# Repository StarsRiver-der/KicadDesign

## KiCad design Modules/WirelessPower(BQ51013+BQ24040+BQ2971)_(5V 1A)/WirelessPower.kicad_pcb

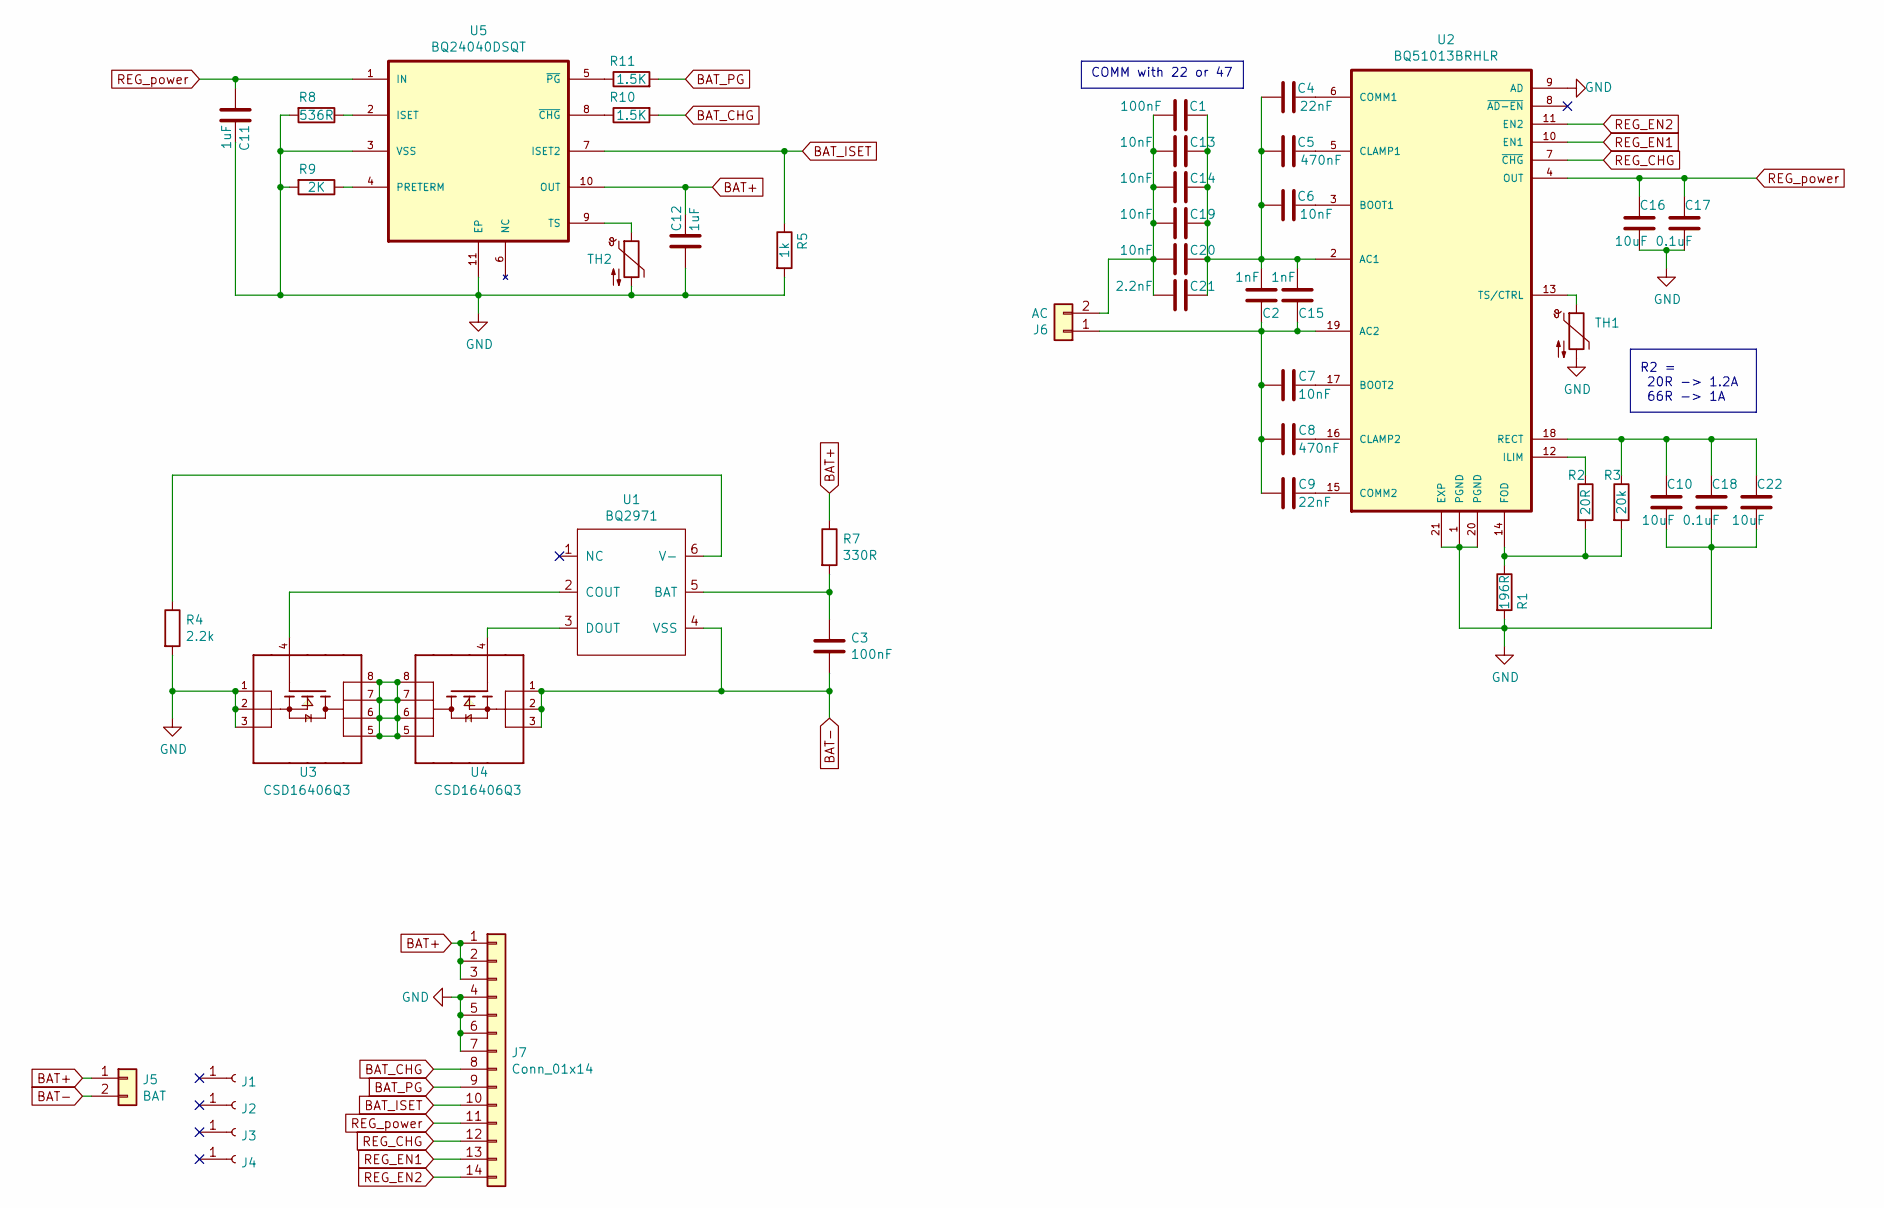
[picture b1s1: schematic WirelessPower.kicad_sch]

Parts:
C1: 100nF; C_1206_3216Metric
C2, C15: 1nF; C_0603_1608Metric
C3: 100nF; C_0402_1005Metric
C4, C9: 22nF; C_0402_1005Metric
C5, C8: 470nF; C_0402_1005Metric
C6, C7: 10nF; C_0402_1005Metric
C10, C16, C22: 10uF; C_0603_1608Metric
C11, C12: 1uF; C_0603_1608Metric
C13, C14, C19, C20: 10nF; C_0603_1608Metric
C17, C18: 0.1uF; C_0603_1608Metric
C21: 2.2nF; C_0603_1608Metric
J1, J2, J3, J4: Conn_01x01_Female; MountingHole_2.2mm_M2
J5: BAT; PinHeader_1x02_P2.54mm_Vertical
J6: AC; R_Axial_DIN0204_L3.6mm_D1.6mm_P2.54mm_Vertical
J7: Conn_01x14; Hirose_FH12-14S-0.5SH_1x14-1MP_P0.50mm_Horizontal
R1: 196R; R_0402_1005Metric
R2: 20R; R_0402_1005Metric
R3: 20k; R_0402_1005Metric
R4: 2.2k; R_0402_1005Metric
R5: 1k; R_0402_1005Metric
R7: 330R; R_0402_1005Metric
R8: 536R; R_0402_1005Metric
R9: 2K; R_0402_1005Metric
R10, R11: 1.5K; R_0402_1005Metric
TH1, TH2: Thermistor_NTC; R_Axial_DIN0204_L3.6mm_D1.6mm_P2.54mm_Vertical
U1: BQ2971; WSON-6_1.5x1.5mm_P0.5mm
U2: BQ51013BRHLR; IC_MSP430FR2522IRHLR
U3, U4: CSD16406Q3
U5: BQ24040DSQT; SON40P200X200X80-11N

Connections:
BAT+: C12.1, J5.1, J7.1, J7.2, J7.3, R7.1, U5.10 (OUT); also elsewhere on the board
BAT-: C3.2, J5.2, U1.4 (VSS), U4.1, U4.2, U4.3; also elsewhere on the board
BAT_CHG: J7.8, R10.2
BAT_ISET: J7.10, R5.1, U5.7 (ISET2)
BAT_PG: J7.9, R11.2
GND: C10.1, C11.1, C12.2, C16.1, C17.1, C18.1, C22.1, J7.4, J7.5, J7.6, J7.7, R1.2, R4.2, R5.2, R8.2, R9.2, TH1.2, TH2.2, U2.1 (PGND), U2.9 (AD), U2.20 (PGND), U2.21 (EXP), U3.1, U3.2, U3.3, U5.3 (VSS), U5.11 (EP)
unnamed: C1.1, C13.1, C14.1, C19.1, C20.1, C21.1, J6.2
unnamed: C1.2, C2.1, C4.1, C5.1, C6.1, C13.2, C14.2, C15.1, C19.2, C20.2, C21.2, U2.2 (AC1)
unnamed: C3.1, R7.2, U1.5 (BAT)
unnamed: C4.2, U2.6 (COMM1)
unnamed: C5.2, U2.5 (CLAMP1)
unnamed: C6.2, U2.3 (BOOT1)
unnamed: C7.1, U2.17 (BOOT2)
unnamed: C8.1, U2.16 (CLAMP2)
unnamed: C9.1, U2.15 (COMM2)
unnamed: C10.2, C18.2, C22.2, R3.1, U2.18 (RECT)
unnamed: C2.2, C7.2, C8.2, C9.2, C15.2, J6.1, U2.19 (AC2)
unnamed: R1.1, R2.2, R3.2, U2.14 (FOD)
unnamed: R2.1, U2.12 (ILIM)
unnamed: R4.1, U1.6 (V-)
unnamed: R8.1, U5.2 (ISET)
unnamed: R9.1, U5.4 (PRETERM)
unnamed: R10.1, U5.8 (~CHG)
unnamed: R11.1, U5.5 (~PG)
unnamed: TH1.1, U2.13 (TS/CTRL)
unnamed: TH2.1, U5.9 (TS)
unnamed: U1.2 (COUT), U3.4
unnamed: U1.3 (DOUT), U4.4
unnamed: U3.5, U3.6, U3.7, U3.8, U4.5, U4.6, U4.7, U4.8
REG_CHG: J7.12, U2.7 (~CHG)
REG_EN1: J7.13, U2.10 (EN1)
REG_EN2: J7.14, U2.11 (EN2)
REG_power: C11.2, C16.2, C17.2, J7.11, U2.4 (OUT), U5.1 (IN)

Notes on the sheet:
R2 = 20R -> 1.2A 66R -> 1A
COMM with 22 or 47

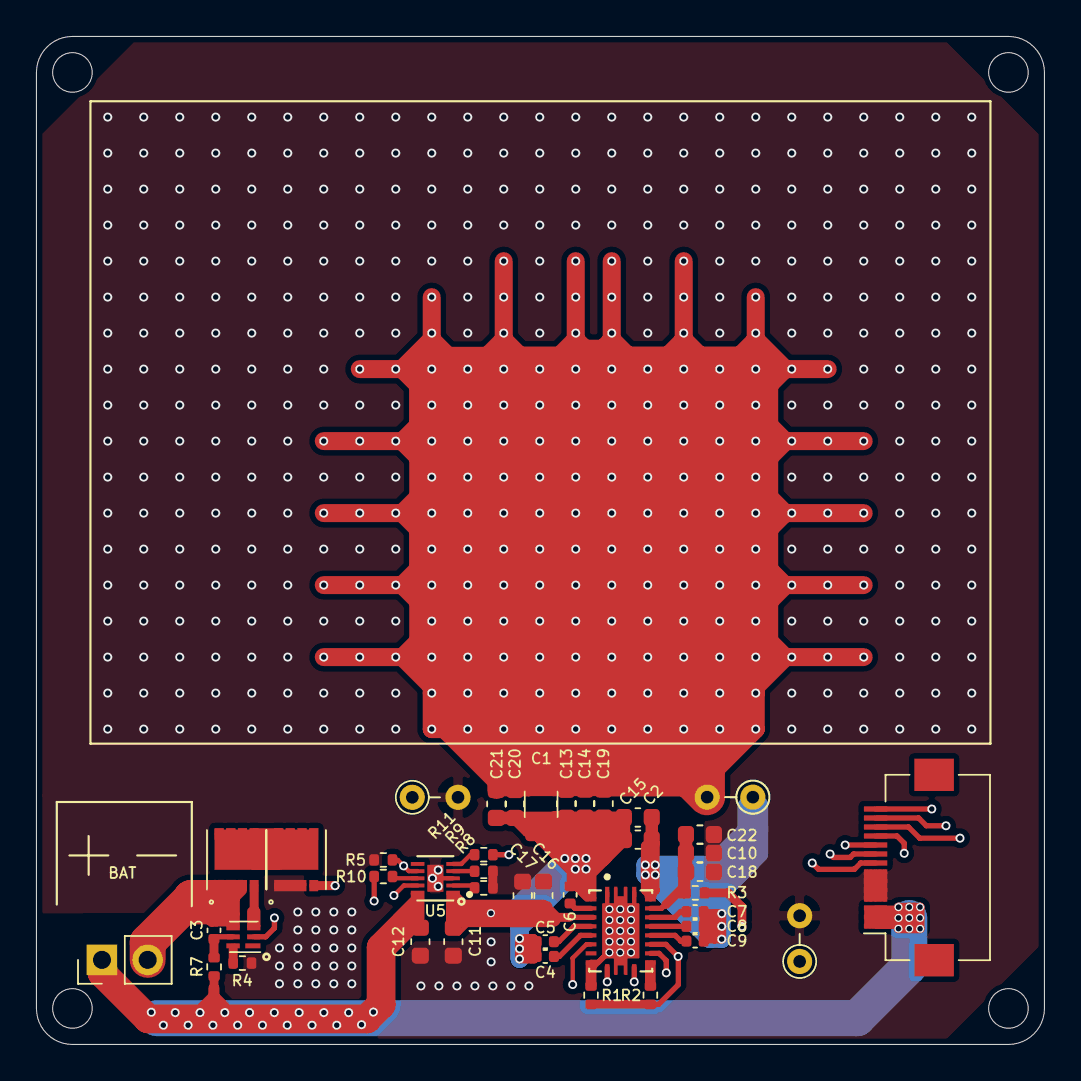
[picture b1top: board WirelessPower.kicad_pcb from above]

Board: 4 copper layers, 56.0 x 56.0 mm, 46 parts (0 on the bottom side), 33 nets.

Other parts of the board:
BAT: BAT; PinHeader_1x02_P2.54mm_Vertical

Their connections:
BAT+: BAT.1; also elsewhere on the board
BAT-: BAT.2; also elsewhere on the board

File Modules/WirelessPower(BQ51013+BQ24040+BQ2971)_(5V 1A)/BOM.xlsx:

代号 | 值 | 类型 | 封装 | 数量 | 单价
C1 | 100nF | C 耐压 50V | 0402 | 100
C2, C15 | 1nF | C 耐压 50V | 0402 | 100
C3 | 0.1uF | C 耐压 50V | 0402 | 100
C4, C9, C14 | 22nF | C 耐压 50V | 0402 | 100
C5, C8 | 470nF | C 耐压 50V | 0402 | 100
C6, C7 | 10nF | C 耐压 50V | 0402 | 100
C10, C16 | 10uF | C 耐压 100V | 0603 | 100
C11, C12 | 1uF | C 耐压 50V | 0402 | 100
C13 | 20nF | C 耐压 50V | 0402 | 100
C17, C18 | 0.1uF | C 耐压 100V | 0603 | 100
R1 | 196R | R | 0402 | 100
R2 | 66R | R | 0402 | 100
R3 | 20k | R | 0402 | 100
R4 | 2.2k | R | 0402 | 100
R5 | 1k | R | 0402 | 100
R7 | 330R | R | 0402 | 100
R8 | 640R | R | 0402 | 100
R9 | 2K | R | 0402 | 100
R10, R11 | 1.5K | R | 0402 | 100
D1 | 红 | LED | 0402 | 50
U2 | BQ51013BRHLR | BQ51013BRHLR | BQ51013BRHLR | 1
U5 | BQ24040DSQT | BQ24040DSQT | BQ24040DSQT | 1
备注：元件用于ESD电路，电容耐压一定要高，防止击穿

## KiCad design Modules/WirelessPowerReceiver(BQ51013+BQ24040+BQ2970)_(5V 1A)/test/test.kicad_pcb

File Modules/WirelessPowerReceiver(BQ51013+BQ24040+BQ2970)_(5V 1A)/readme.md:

# 无线充电接收器
* 工作温度：0-55℃
* 电池直接输出模式
* 电池端最高受电功率 4.1V x 0.98A
* 最高接收功率 5V x 1.12A

# 原理
见说明手册

# 接口
* 电池：2.5mm_2P
* 输出和无线充电电流控制：FPC_Hirose_FH12-14S

# 预览
_(5V%201A)/preview.jpg)

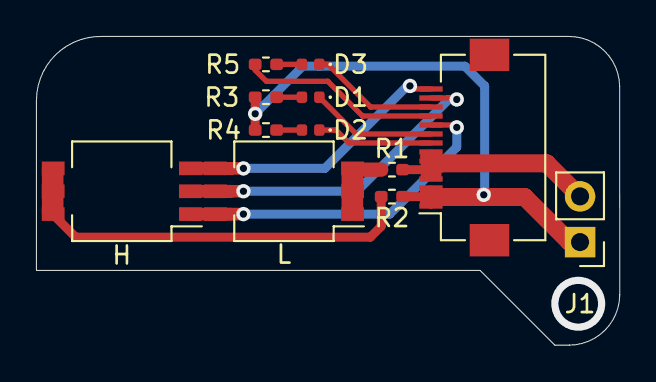
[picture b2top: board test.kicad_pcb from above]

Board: 2 copper layers, 32.4 x 17.1 mm, 12 parts (0 on the bottom side), 14 nets.

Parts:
D1, D2, D3: LED; LED_0402_1005Metric
H: SW_DIP_x03; SW_DIP_SPSTx03_Slide_KingTek_DSHP03TS_W7.62mm_P1.27mm
J1: Conn_01x02; PinHeader_1x02_P2.54mm_Vertical
J7: Conn_01x14; Hirose_FH12-14S-0.5SH_1x14-1MP_P0.50mm_Horizontal
L: SW_DIP_x03; SW_DIP_SPSTx03_Slide_KingTek_DSHP03TS_W7.62mm_P1.27mm
R1, R2: 1K; R_0402_1005Metric_Pad0.72x0.64mm_HandSolder
R3, R4, R5: R; R_0402_1005Metric_Pad0.72x0.64mm_HandSolder

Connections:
BAT+: J1.1, J7.1, J7.2, J7.3, R2.1, R3.2, R4.2
BAT_CHG: D2.1 (K), J7.8
BAT_ISET: H.1, J7.10, L.6
BAT_PG: D1.1 (K), J7.9
GND: J1.2, J7.4, J7.5, J7.6, J7.7, R1.2
unnamed: D1.2 (A), R3.1
unnamed: D2.2 (A), R4.1
unnamed: D3.2 (A), R5.1
unnamed: L.1, L.2, L.3, R1.1
unnamed: H.4, H.5, H.6, R2.2
REG_CHG: D3.1 (K), J7.12
REG_EN1: H.2, J7.13, L.5
REG_EN2: H.3, J7.14, L.4
REG_power: J7.11, R5.2

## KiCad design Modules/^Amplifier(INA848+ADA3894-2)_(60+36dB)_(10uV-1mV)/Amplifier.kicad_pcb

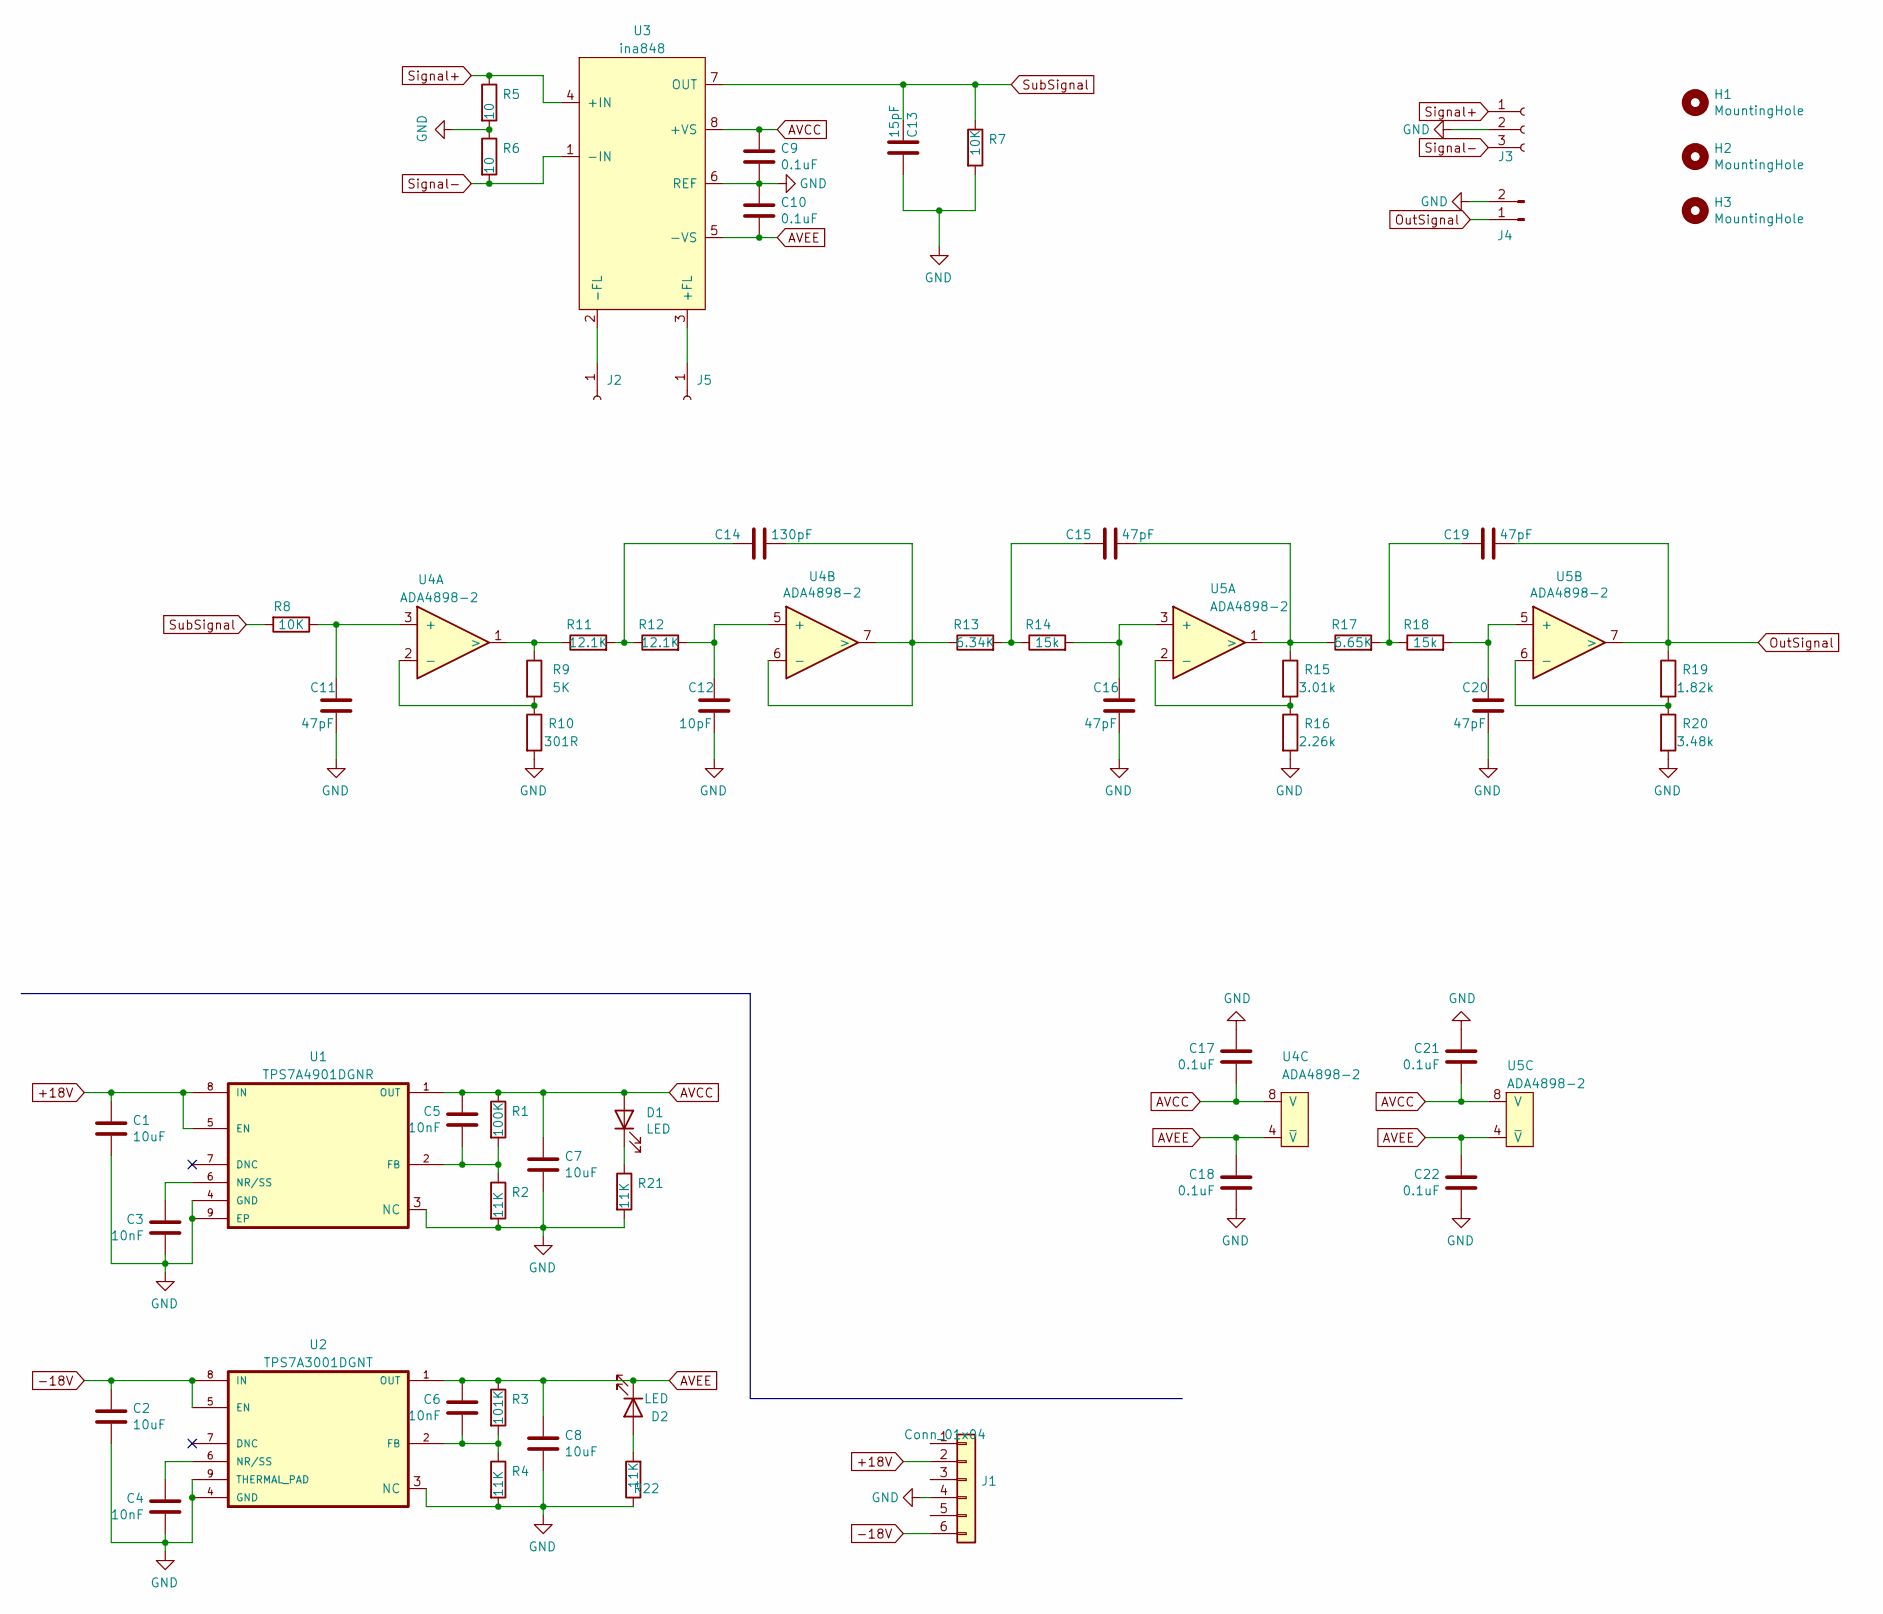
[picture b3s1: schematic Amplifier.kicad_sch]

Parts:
C1, C2, C7, C8: 10uF; C_0603_1608Metric
C3, C4, C5, C6: 10nF; C_0402_1005Metric
C9, C10, C17, C18, C21, C22: 0.1uF; C_1206_3216Metric
C11, C15, C16, C19, C20: 47pF; C_0402_1005Metric
C12: 10pF; C_0402_1005Metric
C13: 15pF; C_0402_1005Metric
C14: 130pF; C_0402_1005Metric
D1, D2: LED; LED_0402_1005Metric
H1, H2, H3: MountingHole; MountingHole_2.2mm_M2
J1: Conn_01x04; Multicomp_MC9A12-1034_2x03_P2.54mm_Vertical
J2, J5: Conn_01x01_Female; MountingPad_1mm
J3: Conn_01x03_Female; PinSocket_1x03_P2.54mm_Vertical
J4: Conn_01x02_Male; SMA_Amphenol_132134_Vertical
R1: 100K; R_0402_1005Metric
R2, R4, R21, R22: 11K; R_0402_1005Metric
R3: 101K; R_0402_1005Metric
R5, R6: 10; R_0402_1005Metric
R7, R8: 10K; R_0402_1005Metric
R9: 5K; R_0402_1005Metric
R10: 301R; R_0402_1005Metric
R11, R12: 12.1K; R_0402_1005Metric
R13: 6.34K; R_0402_1005Metric
R14, R18: 15k; R_0402_1005Metric
R15: 3.01k; R_0402_1005Metric
R16: 2.26k; R_0402_1005Metric
R17: 6.65K; R_0402_1005Metric
R19: 1.82k; R_0402_1005Metric
R20: 3.48k; R_0402_1005Metric
U1: TPS7A4901DGNR; SOP65P490X110-9N
U2: TPS7A3001DGNT; SOP65P490X110-9N
U3: ina848; SOIC-8_3.9x4.9mm_P1.27mm
U4, U5: ADA4898-2; SOIC-8-1EP_3.9x4.9mm_P1.27mm_EP2.29x3mm

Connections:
+18V: C1.1, J1.2, U1.5 (EN), U1.8 (IN)
-18V: C2.1, J1.6, U2.5 (EN), U2.8 (IN)
AVCC: C5.1, C7.1, C9.1, C17.2, C21.2, D1.2 (A), R1.1, U1.1 (OUT), U3.8 (+VS), U4.8 (V), U5.8 (V)
AVEE: C6.1, C8.1, C10.2, C18.1, C22.1, D2.1 (K), R3.1, U2.1 (OUT), U3.5 (-VS), U4.4 (~V), U5.4 (~V)
GND: C1.2, C2.2, C3.2, C4.2, C7.2, C8.2, C9.2, C10.1, C11.2, C12.2, C13.2, C16.2, C17.1, C18.2, C20.2, C21.1, C22.2, J1.4, J3.2, J4.2, R2.2, R4.2, R5.2, R6.1, R7.2, R10.2, R16.2, R20.2, R21.2, R22.1, U1.3 (NC), U1.4 (GND), U1.9 (EP), U2.3 (NC), U2.4 (GND), U2.9 (THERMAL_PAD), U3.6 (REF)
unnamed: C3.1, U1.6 (NR/SS)
unnamed: C4.1, U2.6 (NR/SS)
unnamed: C5.2, R1.2, R2.1, U1.2 (FB)
unnamed: C6.2, R3.2, R4.1, U2.2 (FB)
unnamed: C11.1, R8.1, U4.3 (+)
unnamed: C12.1, R12.2, U4.5 (+)
unnamed: C14.1, R11.2, R12.1
unnamed: C14.2, R13.1, U4.6 (-), U4.7 (>)
unnamed: C15.1, R13.2, R14.1
unnamed: C15.2, R15.1, R17.1, U5.1 (>)
unnamed: C16.1, R14.2, U5.3 (+)
unnamed: C19.1, R17.2, R18.1
unnamed: C20.1, R18.2, U5.5 (+)
unnamed: D1.1 (K), R21.1
unnamed: D2.2 (A), R22.2
unnamed: J2.1, U3.2 (-FL)
unnamed: J5.1, U3.3 (+FL)
unnamed: R9.2, R10.1, U4.2 (-)
unnamed: R9.1, R11.1, U4.1 (>)
unnamed: R15.2, R16.1, U5.2 (-)
unnamed: R19.2, R20.1, U5.6 (-)
OutSignal: C19.2, J4.1, R19.1, U5.7 (>)
Signal+: J3.1, R5.1, U3.4 (+IN)
Signal-: J3.3, R6.2, U3.1 (-IN)
SubSignal: C13.1, R7.1, R8.2, U3.7 (OUT)

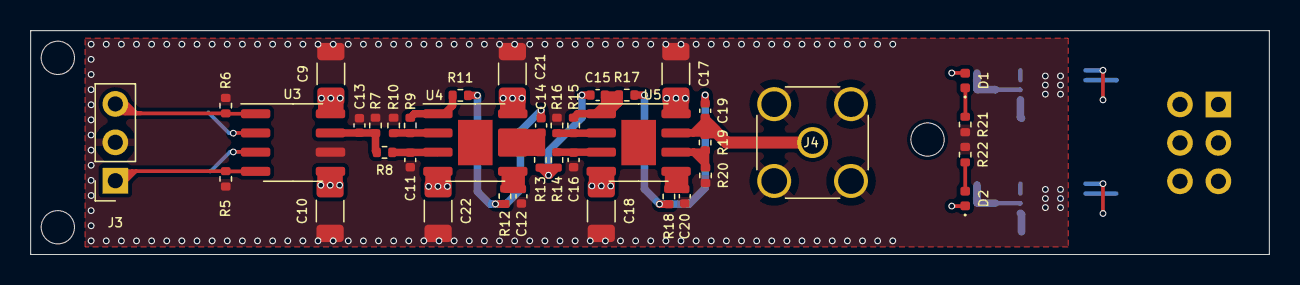
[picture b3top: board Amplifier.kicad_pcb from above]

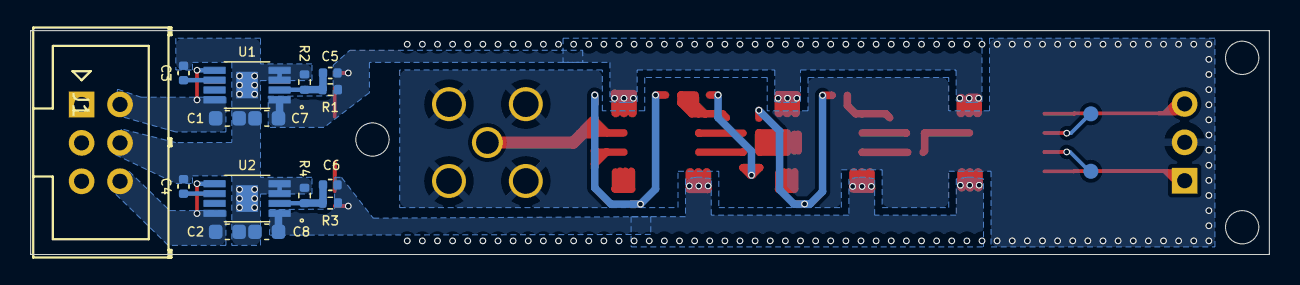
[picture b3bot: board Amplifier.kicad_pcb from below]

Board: 4 copper layers, 81.9 x 14.8 mm, 59 parts (17 on the bottom side), 30 nets.

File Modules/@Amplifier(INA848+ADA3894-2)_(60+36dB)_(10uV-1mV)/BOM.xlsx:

符号 | 数量/板 | 值 | 备注 | 封装 | 数量 | 单价 | 总价
C1, C2, C7, C8 | 4 | 10uF | 25V | 0603 | 100 | 0.1
C3, C4, C5, C6 | 4 | 10nF | 25V | 0402 | 100 | 1.4999999999999999E-2
C9, C10, C17, C18, C21, C22 | 6 | 100nF | 25V COG高频电容 | 1206 | 50
C11, C15, C16, C19, C20 | 5 | 47pF | 25V | 0402 | 100 | 1.4999999999999999E-2
C12 | 1 | 10pF | 25V | 0402 | 100 | 1.4999999999999999E-2
C13 | 1 | 15pF | 25V | 0402 | 100 | 1.4999999999999999E-2
C14 | 1 | 130pF | 25V | 0402 | 100 | 1.4999999999999999E-2
D1, D2 | 2 | LED |  | 0402 | 100
R1 | 1 | 100K |  | 0402 | 100 | 0.01
R2, R4, R21, R22 | 4 | 11K |  | 0402 | 100 | 0.01
R3 | 1 | 101K |  | 0402 | 100 | 0.01
R5, R6 | 2 | 10R |  | 0402 | 100 | 0.01
R7, R8 | 2 | 10K |  | 0402 | 100 | 0.01
R9 | 1 | 5K |  | 0402 | 100 | 0.01
R10 | 1 | 301R |  | 0402 | 100 | 0.01
R11, R12 | 2 | 12.1K |  | 0402 | 100 | 0.01
R13 | 1 | 6.34K |  | 0402 | 100 | 0.01
R14, R18 | 2 | 15k |  | 0402 | 100 | 0.01
R15 | 1 | 3.01k |  | 0402 | 100 | 0.01
R16 | 1 | 2.26k |  | 0402 | 100 | 0.01
R17 | 1 | 6.65K |  | 0402 | 100 | 0.01
R19 | 1 | 1.82k |  | 0402 | 100 | 0.01
R20 | 1 | 3.48k |  | 0402 |  | 0.01
U1 | 1 | TPS7A4901DGNR | TPS7A4901DGNR:TPS7A4901DGNR |  | 5 | 8
U2 | 1 | TPS7A3001DGNT | TPS7A3001DGNT:TPS7A3001DGNT |  | 5 | 8
UX | 1 | ina849 | INA:ina849 | SOIC-8_3.9x4.9mm | 2
U3 | 1 | ina848 | INA:ina848 | SOIC-8_3.9x4.9mm | 2
U4, U5 | 2 | ADA4898-2 | ADA:ADA4898-2 | SOIC-8_3.9x4.9mm | 2

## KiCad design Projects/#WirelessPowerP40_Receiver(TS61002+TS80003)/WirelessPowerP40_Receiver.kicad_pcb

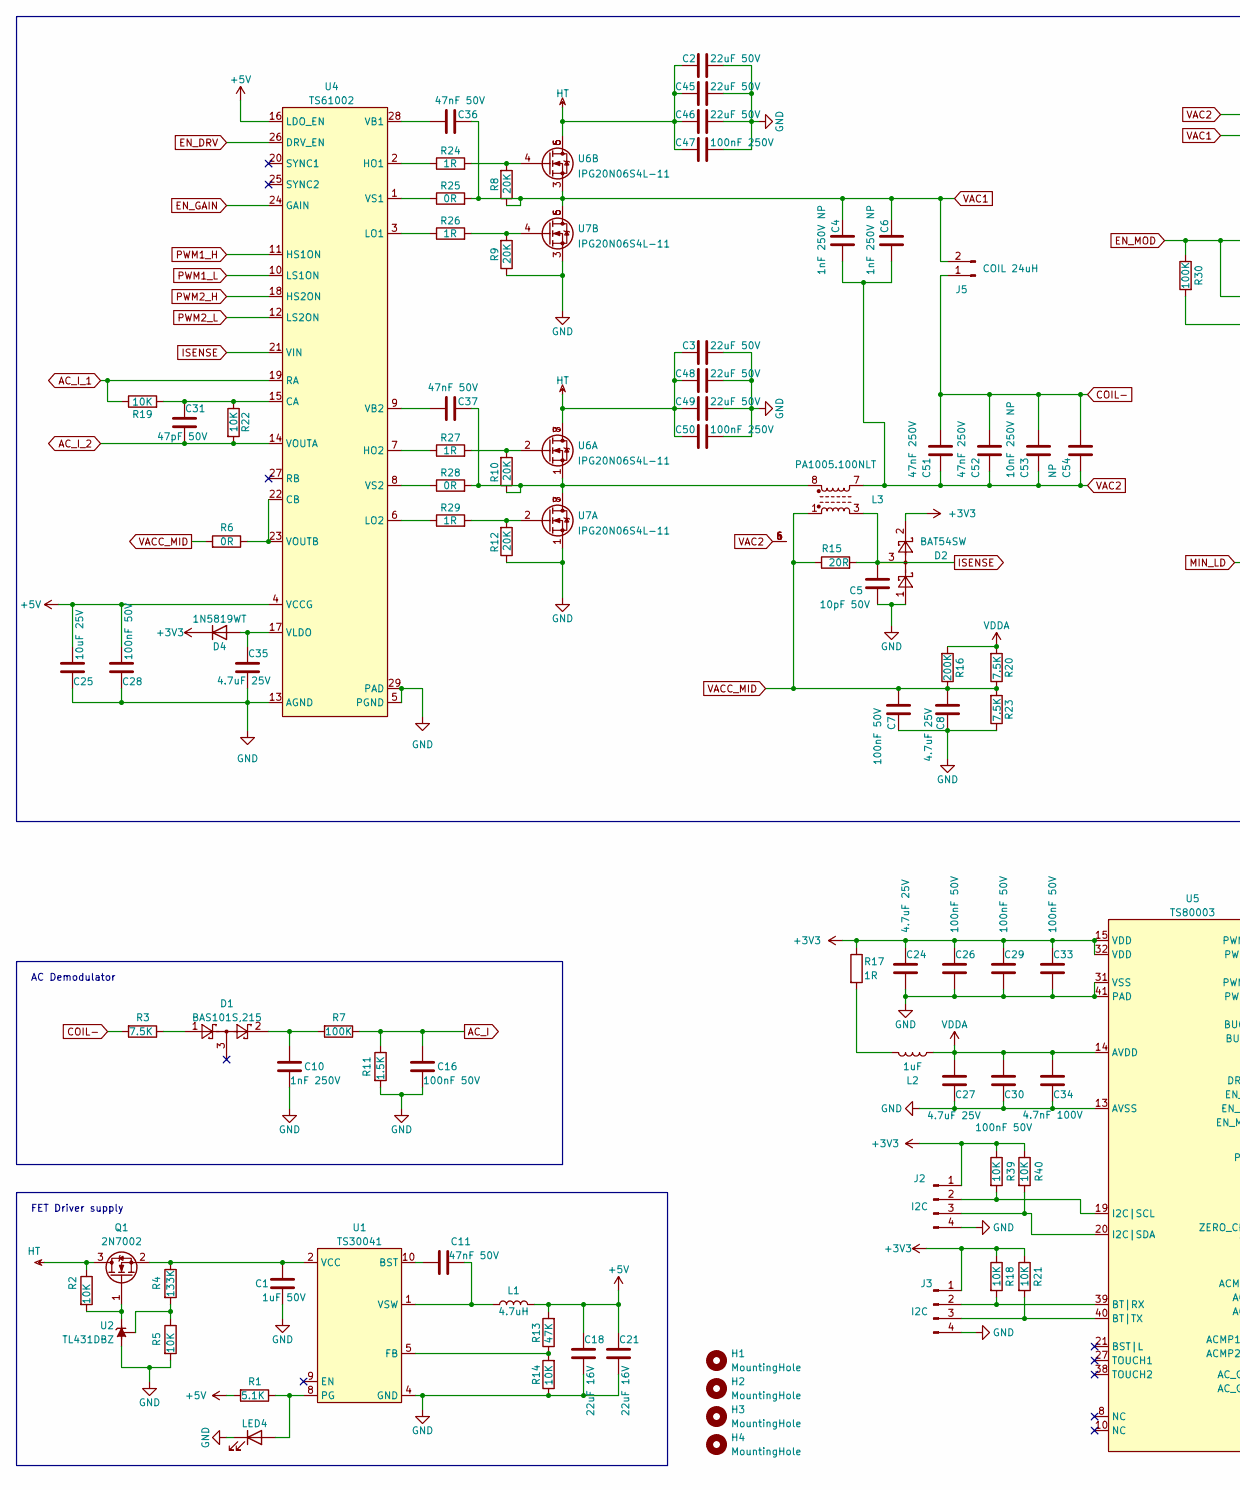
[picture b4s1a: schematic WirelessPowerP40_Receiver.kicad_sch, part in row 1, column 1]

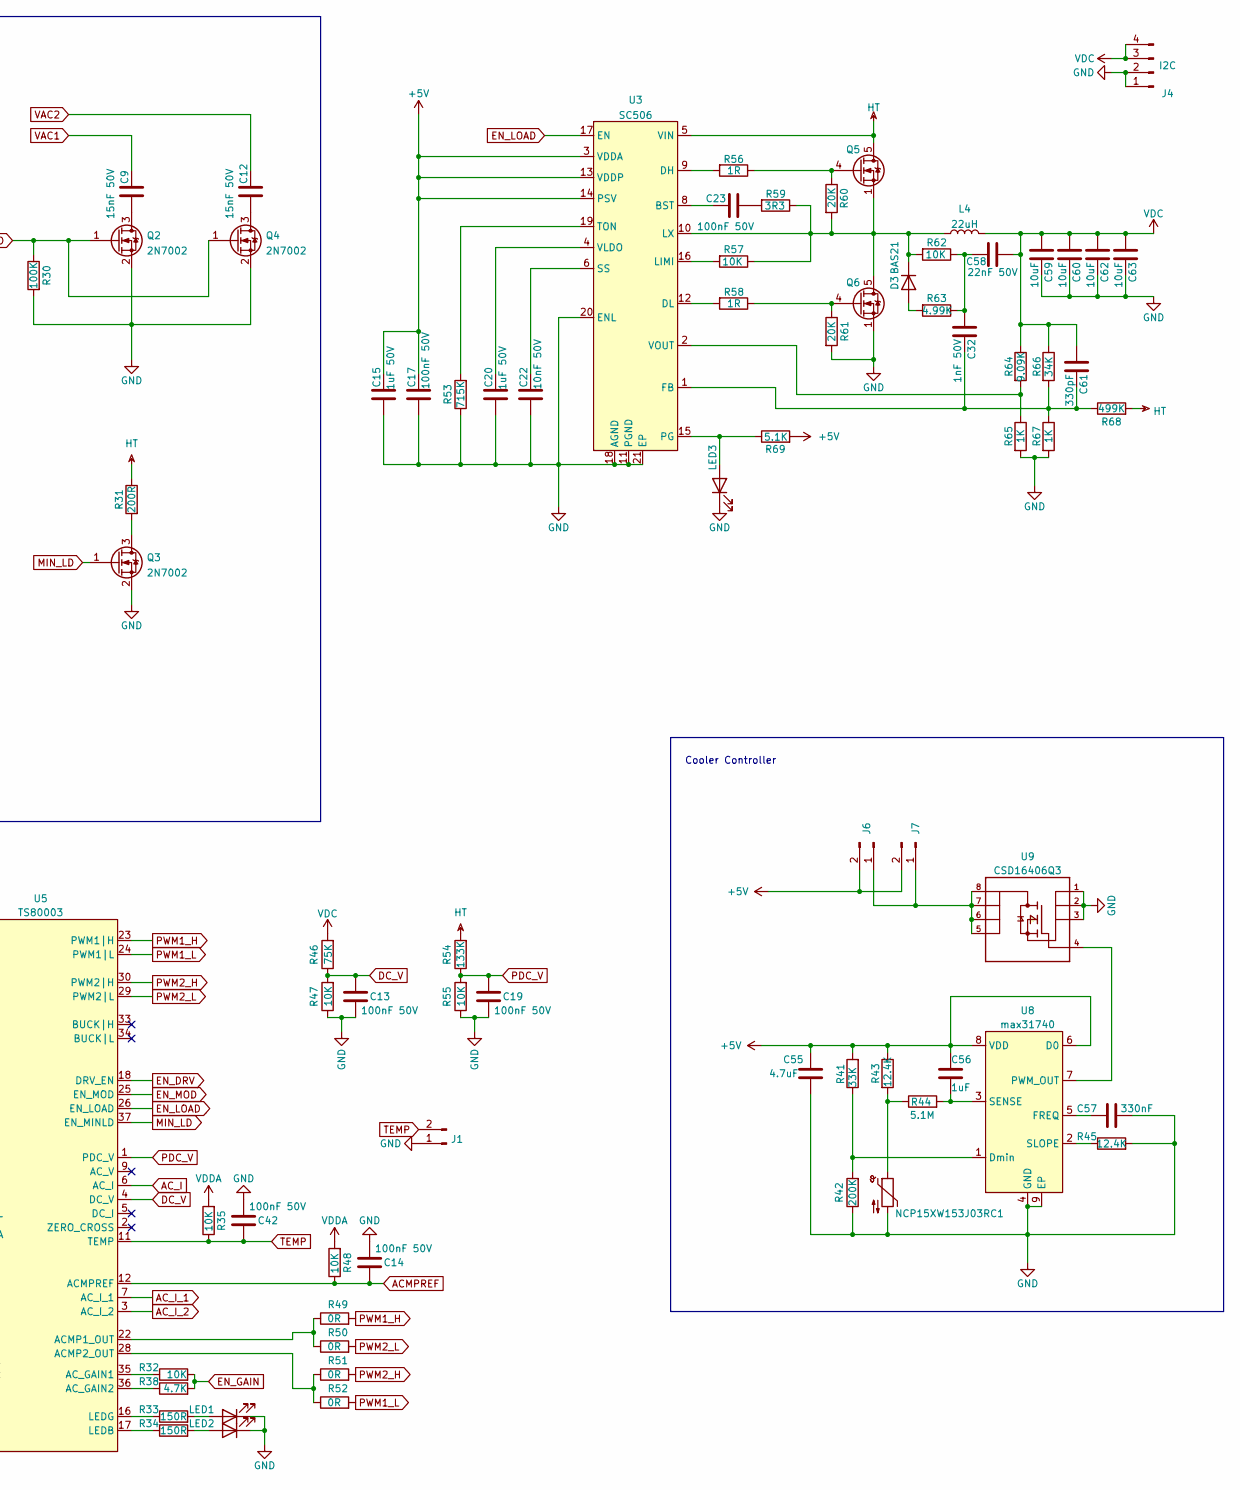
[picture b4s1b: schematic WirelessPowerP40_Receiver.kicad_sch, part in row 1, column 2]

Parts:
C1, C15, C20: 1uF 50V; C_0402_1005Metric
C2, C3, C45, C46, C48, C49: 22uF 50V; C_0805_2012Metric
C4, C6: 1nF 250V NP; C_0603_1608Metric
C5: 10pF 50V; C_0402_1005Metric
C7, C13, C14, C16, C17, C19, C23, C26, C28, C29, C30, C33, C42: 100nF 50V; C_0402_1005Metric
C8, C24, C27, C35: 4.7uF 25V; C_0402_1005Metric
C9, C12: 15nF 50V; C_0402_1005Metric
C10: 1nF 250V; C_0603_1608Metric
C11, C36, C37: 47nF 50V; C_0402_1005Metric
C18, C21: 22uF 16V; C_0603_1608Metric
C22: 10nF 50V; C_0402_1005Metric
C25: 10uF 25V; C_0603_1608Metric
C31: 47pF 50V; C_0402_1005Metric
C32: 1nF 50V; C_0402_1005Metric
C34: 4.7nF 100V; C_0402_1005Metric
C47, C50: 100nF 250V; C_0805_2012Metric
C51, C52: 47nF 250V; C_1210_3225Metric
C53: 10nF 250V NP; C_1210_3225Metric
C54: NP; C_1210_3225Metric
C55: 4.7uF; C_0402_1005Metric
C56: 1uF; C_0402_1005Metric
C57: 330nF; C_0402_1005Metric
C58: 22nF 50V; C_0402_1005Metric
C59, C60, C62, C63: 10uF; C_1206_3216Metric
C61: 330pF; C_0402_1005Metric
D1: BAS101S,215; SOT-23
D2: BAT54SW; SOT-323_SC-70
D3: BAS21; SOT-23
D4: 1N5819WT; D_SOD-523
H1, H2, H3, H4: MountingHole; MountingHole_2.2mm_M2_Pad_Via
J1, J6, J7: Conn_01x02_Male; PinHeader_1x02_P2.00mm_Vertical
J2, J3: I2C; PinHeader_1x04_P2.00mm_Vertical
J4: I2C; SolderWire-0.75sqmm_1x04_P4.8mm_D1.25mm_OD2.3mm
J5: COIL 24uH; AMASS_XT30U-F_1x02_P5.0mm_Vertical
L1: 4.7uH; L_Wuerth_HCI-5040
L2: 1uF; L_Taiyo-Yuden_NR-30xx
L3: PA1005.100NLT; PA1005
L4: 22uH; L_Wuerth_HCI-1350
LED1, LED2, LED3, LED4: LED; LED_0402_1005Metric
NCP15XW153J03RC1: Thermistor_NTC; R_0402_1005Metric
Q1, Q2, Q3, Q4: 2N7002; SOT-23
Q5: BSC100N06L; TDSON-8-1
Q6: BSC028N06L; TDSON-8-1
R1, R69: 5.1K; R_0402_1005Metric
R2, R5, R14, R18, R19, R21, R22, R32, R35, R39, R40, R47, R48, R55, R57, R62: 10K; R_0402_1005Metric
R3, R20, R23: 7.5K; R_0402_1005Metric
R4, R54: 133K; R_0402_1005Metric
R6, R25, R28, R49, R50, R51, R52: 0R; R_0402_1005Metric
R7: 100K; R_0603_1608Metric
R8, R9, R10, R12, R60, R61: 20K; R_0402_1005Metric
R11: 1.5K; R_0402_1005Metric
R13: 47K; R_0402_1005Metric
R15: 20R; R_0603_1608Metric
R16, R42: 200K; R_0402_1005Metric
R17, R24, R26, R27, R29, R56, R58: 1R; R_0402_1005Metric
R30: 100K; R_0402_1005Metric
R31: 200R; R_1812_4532Metric
R33, R34: 150R; R_0402_1005Metric
R38: 4.7K; R_0402_1005Metric
R41: 33K; R_0402_1005Metric
R43, R45: 12.4K; R_0402_1005Metric
R44: 5.1M; R_0402_1005Metric
R46: 75K; R_0402_1005Metric
R53: 715K; R_0402_1005Metric
R59: 3R3; R_0402_1005Metric
R63: 4.99K; R_0402_1005Metric
R64: 9.09K; R_0402_1005Metric
R65, R67: 1K; R_0402_1005Metric
R66: 34K; R_0402_1005Metric
R68: 499K; R_0402_1005Metric
U1: TS30041; QFN-16-1EP_3x3mm_P0.5mm_EP1.7x1.7mm
U2: TL431DBZ; SOT-23
U3: SC506; QFN-20-1EP_3x3mm_P0.4mm_EP1.65x1.65mm
U4: TS61002; QFN-28-1EP_5x5mm_P0.5mm_EP3.35x3.35mm
U5: TS80003; QFN-40-1EP_5x5mm_P0.4mm_EP3.6x3.6mm
U6, U7: IPG20N06S4L-11; Infineon_PG-TISON-8-2-2
U8: max31740; TDFN-8-1EP_3x2mm_P0.5mm_EP1.80x1.65mm
U9: CSD16406Q3

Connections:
+3V3: C24.1, C26.1, C29.1, C33.1, D2.2, D4.1 (K), J2.1, J3.1, R17.1, R18.1, R21.1, R39.1, R40.1, U5.15 (VDD), U5.32 (VDD)
+5V: C15.2, C17.2, C18.1, C21.1, C25.1, C28.1, C55.1, C56.1, J6.2, J7.2, L1.2, R1.2, R13.2, R41.2, R43.1, R69.2, U3.3 (VDDA), U3.13 (VDDP), U3.14 (PSV), U4.4 (VCCG), U4.16 (LDO_EN), U8.6 (D0), U8.8 (VDD)
ACMPREF: C14.1, R48.1, U5.12 (ACMPREF)
AC_I: C16.1, R7.1, R11.1, U5.6 (AC_I)
AC_I_1: R19.1, U4.19 (RA), U5.7 (AC_I_1)
AC_I_2: C31.2, R22.2, U4.14 (VOUTA), U5.3 (AC_I_2)
COIL-: C51.1, C52.1, C53.1, C54.1, J5.1, R3.2
DC_V: C13.2, R46.1, R47.2, U5.4 (DC_V)
EN_DRV: U4.26 (DRV_EN), U5.18 (DRV_EN)
EN_GAIN: R32.2, R38.2, U4.24 (GAIN)
EN_LOAD: U3.17 (EN), U5.26 (EN_LOAD)
EN_MOD: Q2.1 (G), Q4.1 (G), R30.1, U5.25 (EN_MOD)
GND: C1.2, C2.1, C3.1, C5.1, C7.2, C8.2, C10.2, C13.1, C14.2, C15.1, C16.2, C17.1, C18.2, C19.1, C20.1, C21.2, C22.1, C24.2, C25.2, C26.2, C27.2, C28.2, C29.2, C30.2, C33.2, C34.2, C35.2, C42.2, C45.1, C46.1, C47.1, C48.1, C49.1, C50.1, C55.2, C57.2, C59.1, C60.1, C62.1, C63.1, D2.1, J1.1, J2.4, J3.4, J4.1, J4.2, LED1.1 (K), LED2.1 (K), LED3.1 (K), LED4.1 (K), NCP15XW153J03RC1.2, Q2.2 (S), Q3.2 (S), Q4.2 (S), Q6.1 (S), Q6.2 (S), Q6.3 (S), R5.2, R9.1, R11.2, R12.1, R14.1, R23.1, R30.2, R42.1, R45.2, R47.1, R53.1, R55.1, R61.2, R65.2, R67.2, U1.4 (GND), U1.14 (GND), U1.15 (GND), U1.17 (GND), U2.3 (A), U3.11 (PGND), U3.18 (AGND), U3.20 (ENL), U3.21 (EP), U4.5 (PGND), U4.13 (AGND), U4.29 (PAD), U5.13 (AVSS), U5.31 (VSS), U5.41 (PAD), U7.1, U7.3, U8.4 (GND), U8.9 (EP), U9.1, U9.2, U9.3
HT: C2.2, C3.2, C45.2, C46.2, C47.2, C48.2, C49.2, C50.2, Q1.3 (D), Q5.5 (D), R2.1, R31.1, R54.2, R68.2, U3.5 (VIN), U6.5, U6.6, U6.7, U6.8
ISENSE: C5.2, D2.3, L3.3, R15.2, U4.21 (VIN)
MIN_LD: Q3.1 (G), U5.37 (EN_MINLD)
unnamed: C1.1, Q1.2 (S), R4.1, U1.2 (VCC), U1.3 (VCC), U1.11 (VCC)
unnamed: C9.2, Q2.3 (D)
unnamed: C10.1, D1.2, R7.2
unnamed: C11.1, U1.10 (BST)
unnamed: C11.2, L1.1, U1.1 (VSW), U1.12 (VSW), U1.13 (VSW), U1.16 (VSW)
unnamed: C12.2, Q4.3 (D)
unnamed: C20.2, U3.4 (VLDO)
unnamed: C22.2, U3.6 (SS)
unnamed: C23.1, U3.8 (BST)
unnamed: C23.2, R59.2
unnamed: C31.1, R19.2, R22.1, U4.15 (CA)
unnamed: C32.1, C61.1, R66.2, R67.1, R68.1, U3.1 (FB)
unnamed: C32.2, C58.1, R62.1, R63.1
unnamed: C35.1, D4.2 (A), U4.17 (VLDO)
unnamed: C36.1, U4.28 (VB1)
unnamed: C37.1, U4.9 (VB2)
unnamed: C37.2, L3.8, R10.1, R28.2, U6.1, U7.7, U7.8
unnamed: C56.2, R44.2, U8.3 (SENSE)
unnamed: C57.1, U8.5 (FREQ)
unnamed: D1.1, R3.1
unnamed: D3.1 (A), R63.2
unnamed: D3.3 (K), L4.1, Q5.1 (S), Q5.2 (S), Q5.3 (S), Q6.5 (D), R57.1, R59.1, R60.2, R62.2, U3.10 (LX)
unnamed: J2.2, R39.2, U5.19 (I2C|SCL)
unnamed: J2.3, R40.2, U5.20 (I2C|SDA)
unnamed: J3.2, R18.2, U5.39 (BT|RX)
unnamed: J3.3, R21.2, U5.40 (BT|TX)
unnamed: J6.1, J7.1, U9.5, U9.6, U9.7, U9.8
unnamed: L2.2, R17.2
unnamed: LED1.2 (A), R34.2
unnamed: LED2.2 (A), R33.2
unnamed: LED3.2 (A), R69.1, U3.15 (PG)
unnamed: LED4.2 (A), R1.1, U1.8 (PG)
unnamed: NCP15XW153J03RC1.1, R43.2, R44.1
unnamed: Q1.1 (G), R2.2, U2.1 (K)
unnamed: Q3.3 (D), R31.2
unnamed: Q5.4 (G), R56.1, R60.1
unnamed: Q6.4 (G), R58.1, R61.1
unnamed: R4.2, R5.1, U2.2 (REF)
unnamed: R6.1, U4.22 (CB), U4.23 (VOUTB)
unnamed: R10.2, R27.2, U6.2
unnamed: R12.2, R29.2, U7.2
unnamed: R13.1, R14.2, U1.5 (FB)
unnamed: R24.1, U4.2 (HO1)
unnamed: R8.2, R24.2, U6.4
unnamed: R25.1, U4.1 (VS1)
unnamed: R26.1, U4.3 (LO1)
unnamed: R9.2, R26.2, U7.4
unnamed: R27.1, U4.7 (HO2)
unnamed: R28.1, U4.8 (VS2)
unnamed: R29.1, U4.6 (LO2)
unnamed: R32.1, U5.35 (AC_GAIN1)
unnamed: R33.1, U5.16 (LEDG)
unnamed: R34.1, U5.17 (LEDB)
unnamed: R38.1, U5.36 (AC_GAIN2)
unnamed: R41.1, R42.2, U8.1 (Dmin)
unnamed: R45.1, U8.2 (SLOPE)
unnamed: R49.1, R50.1, U5.22 (ACMP1_OUT)
unnamed: R51.1, R52.1, U5.28 (ACMP2_OUT)
unnamed: R53.2, U3.19 (TON)
unnamed: R56.2, U3.9 (DH)
unnamed: R57.2, U3.16 (LIMI)
unnamed: R58.2, U3.12 (DL)
unnamed: R64.2, R65.1, U3.2 (VOUT)
unnamed: U8.7 (PWM_OUT), U9.4
PDC_V: C19.2, R54.1, R55.2, U5.1 (PDC_V)
PWM1_H: R49.2, U4.11 (HS1ON), U5.23 (PWM1|H)
PWM1_L: R52.2, U4.10 (LS1ON), U5.24 (PWM1|L)
PWM2_H: R51.2, U4.18 (HS2ON), U5.30 (PWM2|H)
PWM2_L: R50.2, U4.12 (LS2ON), U5.29 (PWM2|L)
TEMP: C42.1, J1.2, R35.1, U5.11 (TEMP)
VAC1: C4.1, C6.1, C9.1, C36.2, J5.2, R8.1, R25.2, U6.3, U7.5, U7.6
VAC2: C4.2, C6.2, C12.1, C51.2, C52.2, C53.2, C54.2, L3.4, L3.5, L3.6, L3.7
VACC_MID: C7.1, C8.1, L3.1, R6.2, R15.1, R16.1, R20.1, R23.2
VDC: C58.2, C59.2, C60.2, C61.2, C62.2, C63.2, J4.3, J4.4, L4.2, R46.2, R64.1, R66.1
VDDA: C27.1, C30.1, C34.1, L2.1, R16.2, R20.2, R35.2, R48.2, U5.14 (AVDD)

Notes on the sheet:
Cooler Controller
AC Demodulator
FET Driver supply

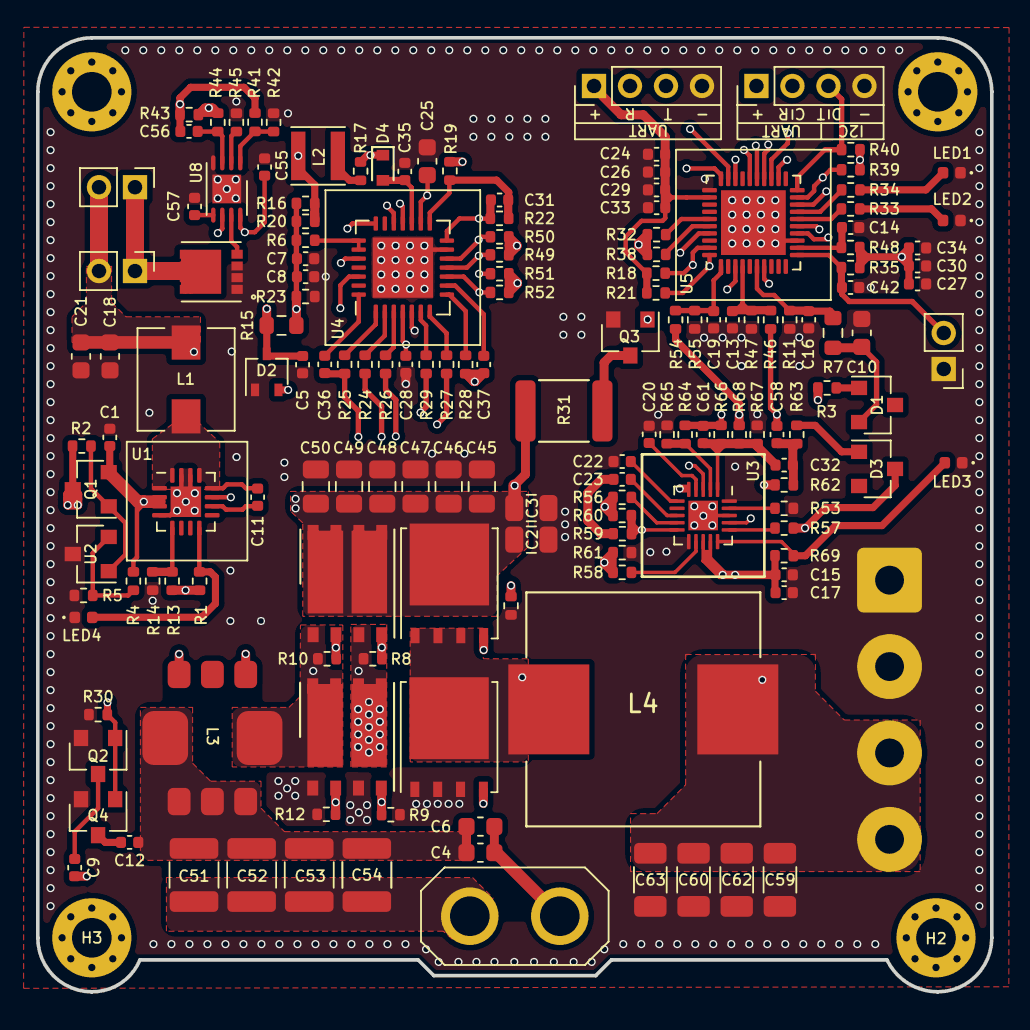
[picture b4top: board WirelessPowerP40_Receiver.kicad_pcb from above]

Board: 4 copper layers, 53.0 x 53.0 mm, 163 parts (0 on the bottom side), 91 nets.
